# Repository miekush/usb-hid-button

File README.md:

# USB HID Button
Simple Programmable USB HID Button based on the Atmel ATMEGA32u4

# PCB

# Programming

In order to minimize the board footprint as much as possible, I decided to program the device over USB using the factory DFU bootloader that comes preprogrammed on the ATMEGA32u4. This eliminates the need for an ICSP header footprint which frees up some space. RESET and HWB are available on test points to enter the device into the DFU bootloader mode.

# License

MKE supports the open source hardware community by sharing hardware design files freely on GitHub!

Please support MKE by purchasing products on [Tindie](https://www.tindie.com/stores/mkengineering/)!

Designed by Mike Kushnerik (miekush)

Licensed under [Creative Commons Attribution-ShareAlike CC BY-SA 4.0](http://creativecommons.org/licenses/by-sa/4.0/)

All text above must be included in any redistribution!

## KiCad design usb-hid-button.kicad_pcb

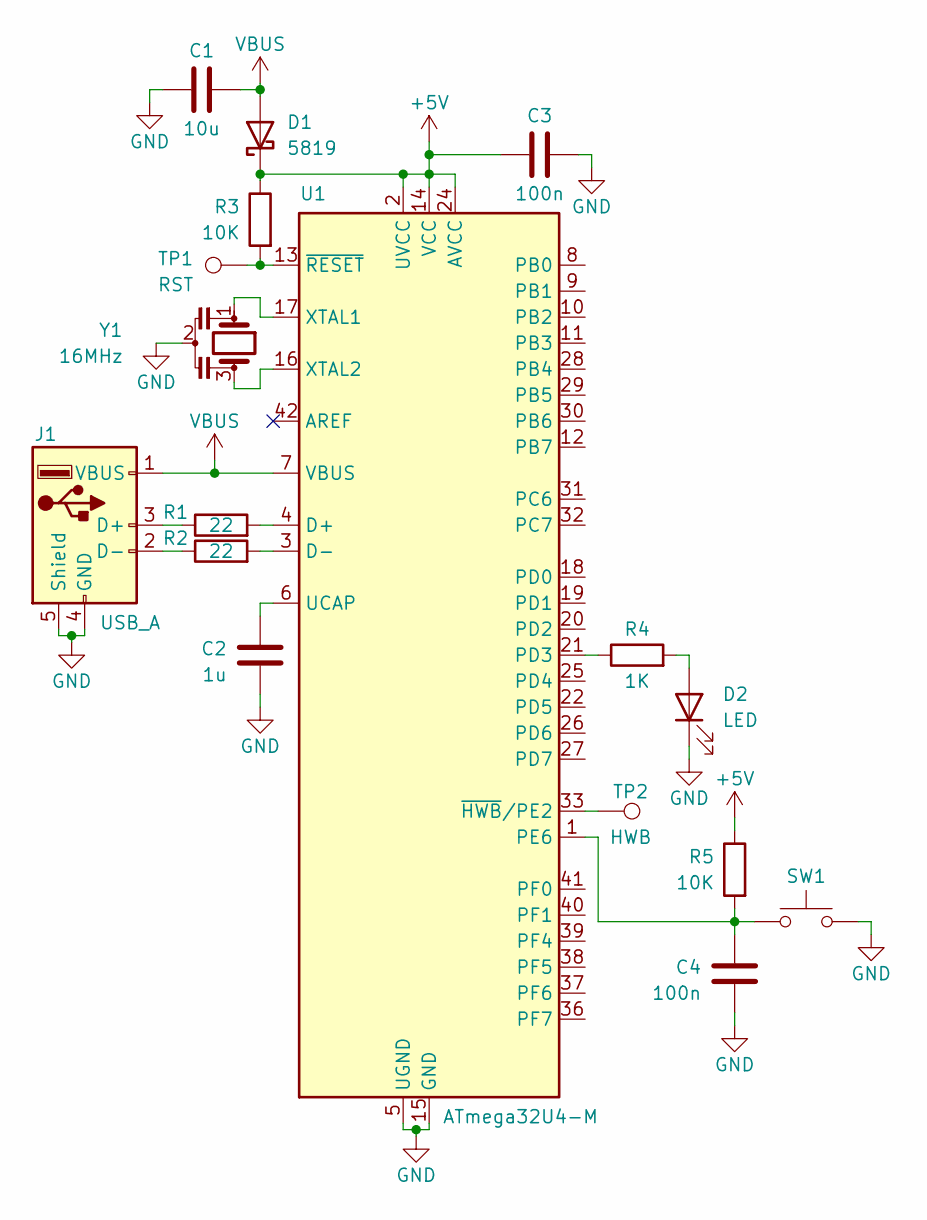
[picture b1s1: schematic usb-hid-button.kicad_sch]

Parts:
C1: 10u; C_0805_2012Metric
C2: 1u; C_0603_1608Metric
C3, C4: 100n; C_0603_1608Metric
D1: 5819; D_SOD-323
D2: LED; LED_0603_1608Metric
J1: USB_A; MOLEX_48037-0001
R1, R2: 22; R_0603_1608Metric
R3, R5: 10K; R_0603_1608Metric
R4: 1K; R_0603_1608Metric
SW1: SW_Push; SW_Push_1P1T_NO_6x6mm_H9.5mm
TP1: RST; PinHeader_1x01_P2.54mm_Vertical
TP2: HWB; PinHeader_1x01_P2.54mm_Vertical
U1: ATmega32U4-M; QFN-44-1EP_7x7mm_P0.5mm_EP5.2x5.2mm
Y1: 16MHz; OSC_CSTNE16M0VH3C000R0

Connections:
+5V: C3.1, D1.1 (K), R3.1, R5.1, U1.2 (UVCC), U1.14 (VCC), U1.24 (AVCC), U1.34 (VCC), U1.44 (AVCC)
GND: C1.1, C2.2, C3.2, C4.2, D2.1 (K), J1.4 (GND), J1.5 (Shield), SW1.2, U1.5 (UGND), U1.15 (GND), U1.23 (GND), U1.35 (GND), U1.43 (GND), U1.45 (GND), Y1.2
unnamed: C2.1, U1.6 (UCAP)
unnamed: D2.2 (A), R4.2
unnamed: J1.2 (D-), R2.1
unnamed: J1.3 (D+), R1.1
unnamed: R1.2, U1.4 (D+)
unnamed: R2.2, U1.3 (D-)
unnamed: R3.2, TP1.1, U1.13 (~RESET)
unnamed: R4.1, U1.21 (PD3)
unnamed: C4.1, R5.2, SW1.1, U1.1 (PE6)
unnamed: U1.16 (XTAL2), Y1.3
unnamed: U1.17 (XTAL1), Y1.1
unnamed: TP2.1, U1.33 (~HWB/PE2)
VBUS: C1.2, D1.2 (A), J1.1 (VBUS), U1.7 (VBUS)

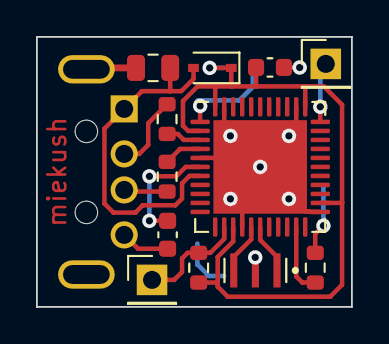
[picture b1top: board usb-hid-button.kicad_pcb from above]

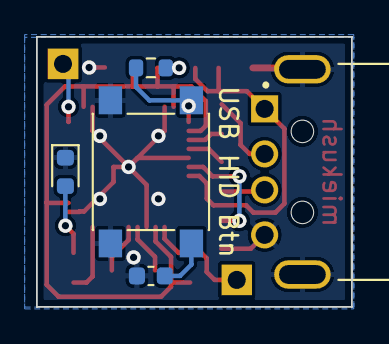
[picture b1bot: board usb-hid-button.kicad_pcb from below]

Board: 2 copper layers, 17.5 x 15.0 mm, 17 parts (5 on the bottom side), 15 nets.

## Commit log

2023-02-05 Initial upload
